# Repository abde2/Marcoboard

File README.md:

# Marcoboard
 This is going to be my first deep delve into keyboard design. I am going to be creating most of this myself using ai03 PCB design guides and other guides that will help me along the way. This would be much simpler if I could use a pro micro and socket it onto the board but I need a total of 27 usable pins, along with it being a DIP package as I suck at soldering surface mount chips.
 The keyboard itself will be a 65% keyboard that will utilise 2 rotary encoders, with push switches, along with an OLED screen inbetween them so that you can easily tell which layer you are on. 
 RGB lighting may also be included if I can figure it out but it isn't exactly necessary. I may only create a capslock light for it.
 This is going to be useful for flashing the bootloader onto it. https://www.instructables.com/id/Burning-Arduino-Bootloader-to-Atmega-32A-PU-Using-/
 http://vusb.wikidot.com/hardware
 https://www.reddit.com/r/MechanicalKeyboards/comments/5xubd7/adding_oled_display_to_your_build_using_qmk/

 Current Progress:
 The first revision of the development board is finished. This is so that I can hand solder the components because I won't be able to manage QFN packages.

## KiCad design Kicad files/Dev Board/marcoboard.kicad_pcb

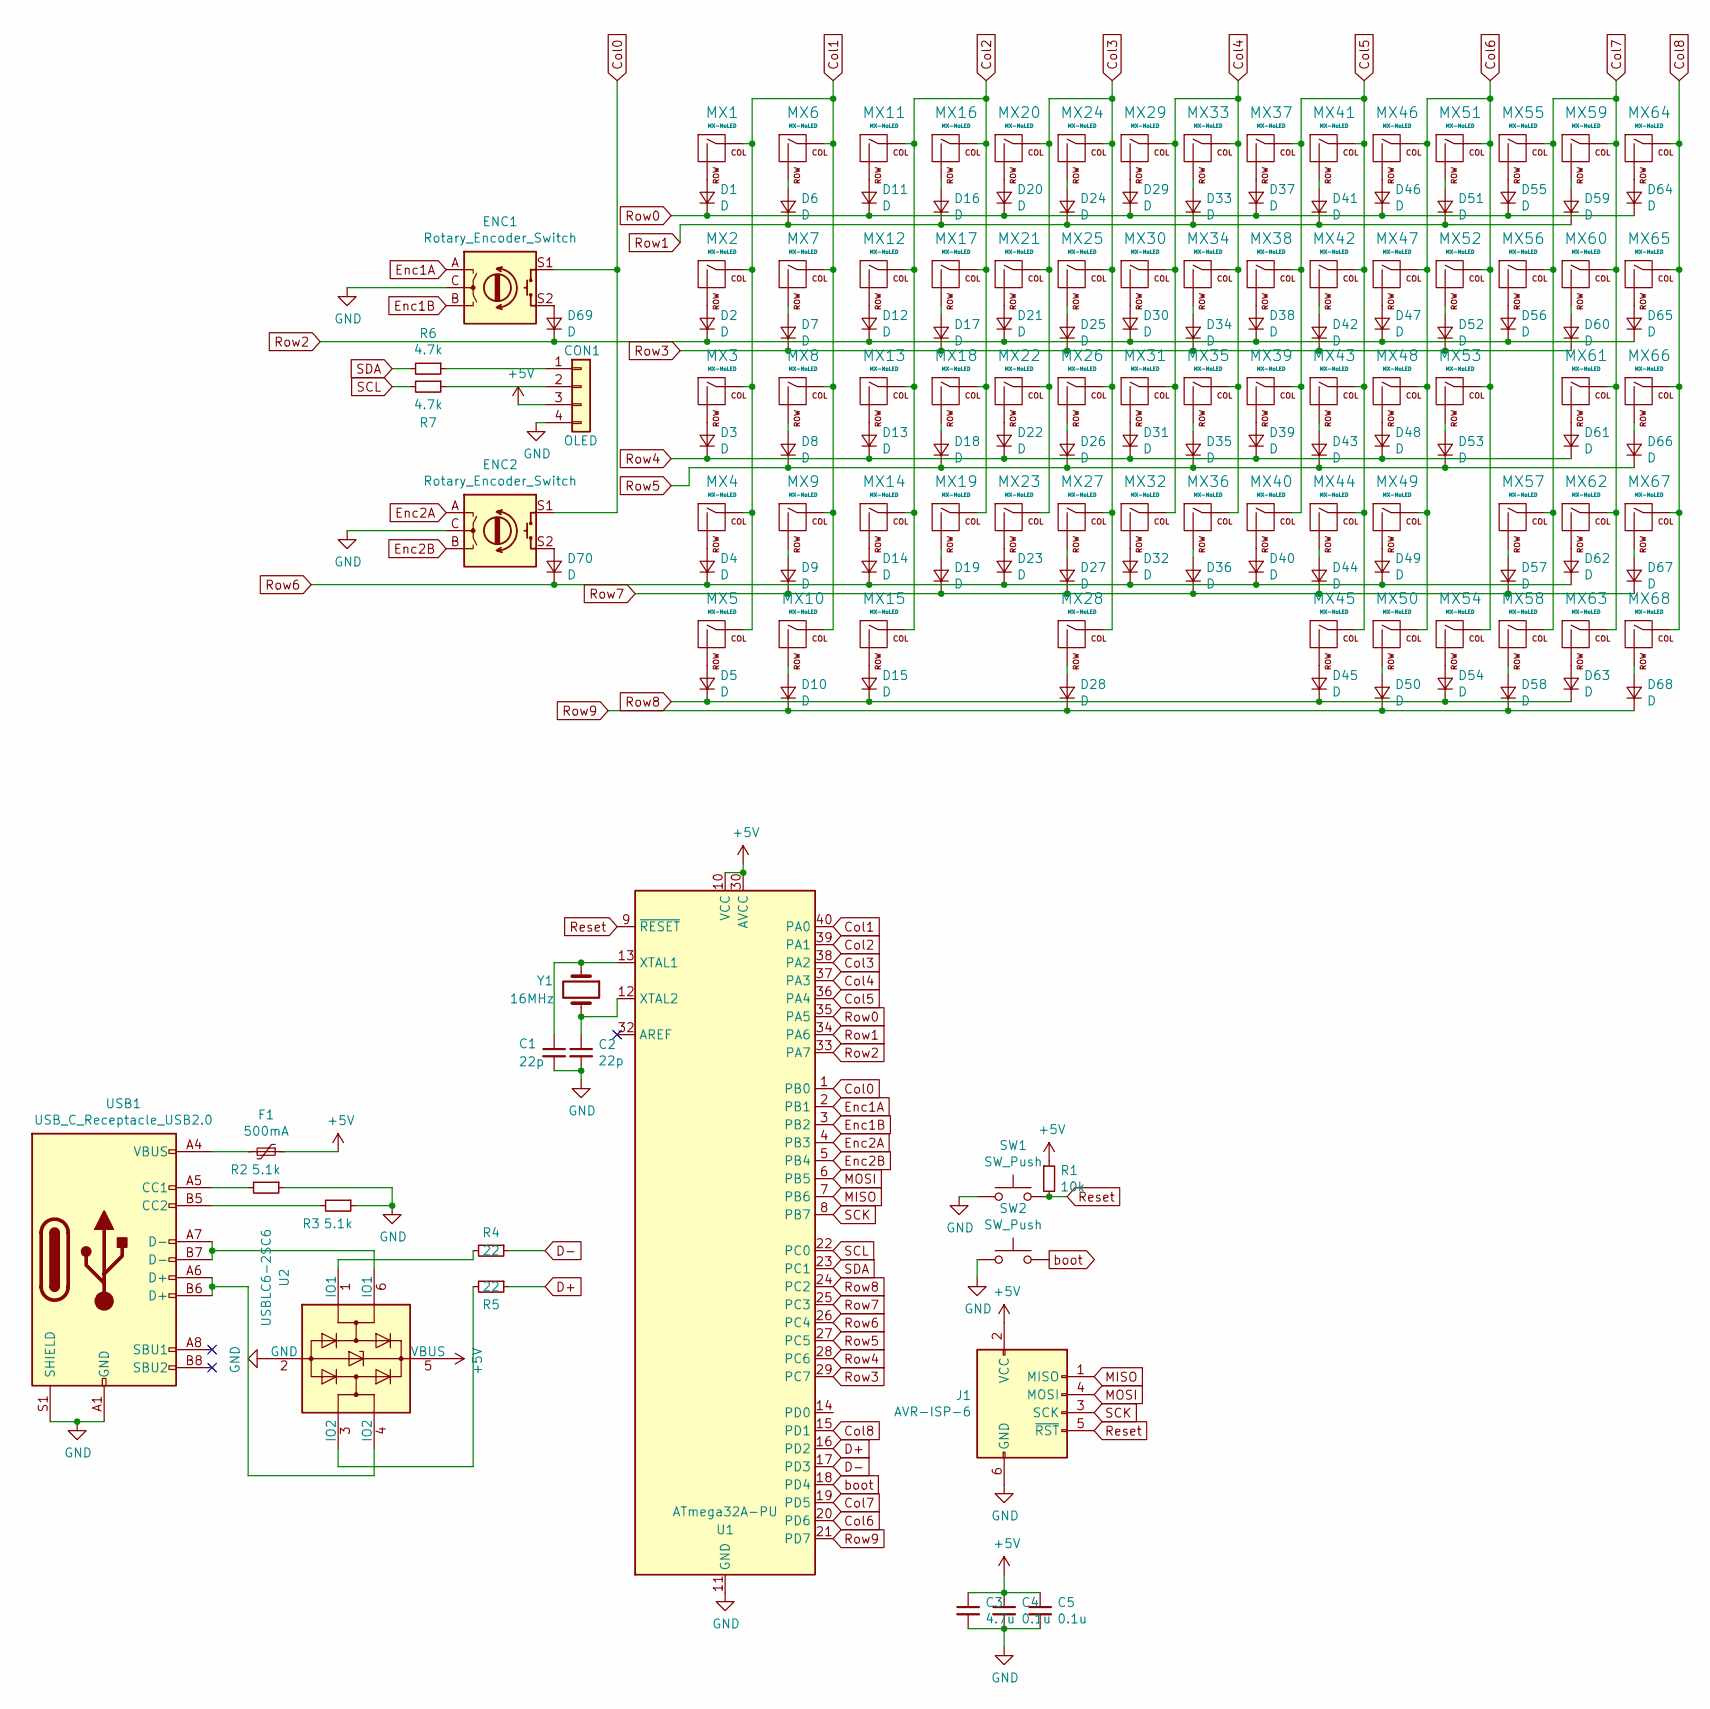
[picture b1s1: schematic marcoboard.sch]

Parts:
C1, C2: 22p; C_0603_1608Metric
C3: 4.7u; C_0603_1608Metric
C4, C5: 0.1u; C_0603_1608Metric
CON1: OLED; 128x32OLED
D1, D2, D3, D4, D5, D6, D7, D8, D9, D10, D11, D12, D13, D14, D15, D16, D17, D18, D19, D20, D21, D22, D23, D24, D25, D26, D27, D28, D29, D30, D31, D32, D33, D34, D35, D36, D37, D38, D39, D40, D41, D42, D43, D44, D45, D46, D47, D48, D49, D50, D51, D52, D53, D54, D55, D56, D57, D58, D59, D60, D61, D62, D63, D64, D65, D66, D67, D68, D69, D70: D; D_SC79
ENC1, ENC2: Rotary_Encoder_Switch; RotaryEncoder_Alps_EC11E-Switch_Vertical_H20mm
F1: 500mA; Fuse_0603_1608Metric
J1: AVR-ISP-6; PinHeader_2x03_P2.00mm_Vertical
MX1, MX6, MX7, MX8, MX9, MX11, MX12, MX13, MX14, MX16, MX17, MX18, MX19, MX20, MX21, MX22, MX23, MX24, MX25, MX26, MX27, MX29, MX30, MX31, MX32, MX33, MX34, MX35, MX36, MX37, MX38, MX39, MX40, MX41, MX42, MX43, MX44, MX45, MX46, MX47, MX48, MX49, MX50, MX51, MX52, MX53, MX54, MX55, MX56, MX58, MX62, MX63, MX64, MX65, MX66, MX67, MX68: MX-NoLED; SW_Cherry_MX_1.00u_Plate
MX2, MX60: MX-NoLED; SW_Cherry_MX_1.50u_Plate
MX3, MX57: MX-NoLED; SW_Cherry_MX_1.75u_Plate
MX4, MX61: MX-NoLED; SW_Cherry_MX_2.25u_Plate
MX5, MX10, MX15: MX-NoLED; SW_Cherry_MX_1.25u_Plate
MX28: MX-NoLED; SW_Cherry_MX_6.25u_Plate
MX59: MX-NoLED; SW_Cherry_MX_2.00u_Plate
R1: 10k; R_0603_1608Metric
R2, R3: 5.1k; R_0603_1608Metric
R4, R5: 22; R_0603_1608Metric
R6, R7: 4.7k; R_0603_1608Metric
SW1, SW2: SW_Push; SW_PUSH_6mm
U1: ATmega32A-PU; DIP-40_W15.24mm
U2: USBLC6-2SC6; SOT-23-6
USB1: USB_C_Receptacle_USB2.0; USB_C_GCT_USB4085
Y1: 16MHz; Crystal_HC49-U_Vertical

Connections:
+5V: C3.1, C4.1, C5.1, CON1.3, F1.1, J1.2 (VCC), R1.1, U1.10 (VCC), U1.30 (AVCC), U2.5 (VBUS)
Col0: ENC1.S1, ENC2.S1, U1.1 (PB0)
Col1: MX1.1 (COL), MX2.1 (COL), MX3.1 (COL), MX4.1 (COL), MX5.1 (COL), MX6.1 (COL), MX7.1 (COL), MX8.1 (COL), MX9.1 (COL), MX10.1 (COL), U1.40 (PA0)
Col2: MX11.1 (COL), MX12.1 (COL), MX13.1 (COL), MX14.1 (COL), MX15.1 (COL), MX16.1 (COL), MX17.1 (COL), MX18.1 (COL), MX19.1 (COL), U1.39 (PA1)
Col3: MX20.1 (COL), MX21.1 (COL), MX22.1 (COL), MX23.1 (COL), MX24.1 (COL), MX25.1 (COL), MX26.1 (COL), MX27.1 (COL), MX28.1 (COL), U1.38 (PA2)
Col4: MX29.1 (COL), MX30.1 (COL), MX31.1 (COL), MX32.1 (COL), MX33.1 (COL), MX34.1 (COL), MX35.1 (COL), MX36.1 (COL), U1.37 (PA3)
Col5: MX37.1 (COL), MX38.1 (COL), MX39.1 (COL), MX40.1 (COL), MX41.1 (COL), MX42.1 (COL), MX43.1 (COL), MX44.1 (COL), MX45.1 (COL), U1.36 (PA4)
Col6: MX46.1 (COL), MX47.1 (COL), MX48.1 (COL), MX49.1 (COL), MX50.1 (COL), MX51.1 (COL), MX52.1 (COL), MX53.1 (COL), MX54.1 (COL), U1.20 (PD6)
Col7: MX55.1 (COL), MX56.1 (COL), MX57.1 (COL), MX58.1 (COL), MX59.1 (COL), MX60.1 (COL), MX61.1 (COL), MX62.1 (COL), MX63.1 (COL), U1.19 (PD5)
Col8: MX64.1 (COL), MX65.1 (COL), MX66.1 (COL), MX67.1 (COL), MX68.1 (COL), U1.15 (PD1)
D+: R5.1, U1.16 (PD2)
D-: R4.1, U1.17 (PD3)
Enc1A: ENC1.A, U1.2 (PB1)
Enc1B: ENC1.B, U1.3 (PB2)
Enc2A: ENC2.A, U1.4 (PB3)
Enc2B: ENC2.B, U1.5 (PB4)
GND: C1.2, C2.2, C3.2, C4.2, C5.2, CON1.4, ENC1.C, ENC2.C, J1.6 (GND), R2.1, R3.1, SW1.1, SW2.1, U1.11 (GND), U1.31 (GND), U2.2 (GND), USB1.A1 (GND), USB1.A12 (GND), USB1.B1 (GND), USB1.B12 (GND), USB1.S1 (SHIELD)
MISO: J1.1 (MISO), U1.7 (PB6)
MOSI: J1.4 (MOSI), U1.6 (PB5)
unnamed: C1.1, U1.13 (XTAL1), Y1.1
unnamed: C2.1, U1.12 (XTAL2), Y1.2
unnamed: CON1.1, R6.1
unnamed: CON1.2, R7.1
unnamed: D1.2 (A), MX1.2 (ROW)
unnamed: D2.2 (A), MX2.2 (ROW)
unnamed: D3.2 (A), MX3.2 (ROW)
unnamed: D4.2 (A), MX4.2 (ROW)
unnamed: D5.2 (A), MX5.2 (ROW)
unnamed: D6.2 (A), MX6.2 (ROW)
unnamed: D7.2 (A), MX7.2 (ROW)
unnamed: D8.2 (A), MX8.2 (ROW)
unnamed: D9.2 (A), MX9.2 (ROW)
unnamed: D10.2 (A), MX10.2 (ROW)
unnamed: D11.2 (A), MX11.2 (ROW)
unnamed: D12.2 (A), MX12.2 (ROW)
unnamed: D13.2 (A), MX13.2 (ROW)
unnamed: D14.2 (A), MX14.2 (ROW)
unnamed: D15.2 (A), MX15.2 (ROW)
unnamed: D16.2 (A), MX16.2 (ROW)
unnamed: D17.2 (A), MX17.2 (ROW)
unnamed: D18.2 (A), MX18.2 (ROW)
unnamed: D19.2 (A), MX19.2 (ROW)
unnamed: D20.2 (A), MX20.2 (ROW)
unnamed: D21.2 (A), MX21.2 (ROW)
unnamed: D22.2 (A), MX22.2 (ROW)
unnamed: D23.2 (A), MX23.2 (ROW)
unnamed: D24.2 (A), MX24.2 (ROW)
unnamed: D25.2 (A), MX25.2 (ROW)
unnamed: D26.2 (A), MX26.2 (ROW)
unnamed: D27.2 (A), MX27.2 (ROW)
unnamed: D28.2 (A), MX28.2 (ROW)
unnamed: D29.2 (A), MX29.2 (ROW)
unnamed: D30.2 (A), MX30.2 (ROW)
unnamed: D31.2 (A), MX31.2 (ROW)
unnamed: D32.2 (A), MX32.2 (ROW)
unnamed: D33.2 (A), MX33.2 (ROW)
unnamed: D34.2 (A), MX34.2 (ROW)
unnamed: D35.2 (A), MX35.2 (ROW)
unnamed: D36.2 (A), MX36.2 (ROW)
unnamed: D37.2 (A), MX37.2 (ROW)
unnamed: D38.2 (A), MX38.2 (ROW)
unnamed: D39.2 (A), MX39.2 (ROW)
unnamed: D40.2 (A), MX40.2 (ROW)
unnamed: D41.2 (A), MX41.2 (ROW)
unnamed: D42.2 (A), MX42.2 (ROW)
unnamed: D43.2 (A), MX43.2 (ROW)
unnamed: D44.2 (A), MX44.2 (ROW)
unnamed: D45.2 (A), MX45.2 (ROW)
unnamed: D46.2 (A), MX46.2 (ROW)
unnamed: D47.2 (A), MX47.2 (ROW)
unnamed: D48.2 (A), MX48.2 (ROW)
unnamed: D49.2 (A), MX49.2 (ROW)
unnamed: D50.2 (A), MX50.2 (ROW)
unnamed: D51.2 (A), MX51.2 (ROW)
unnamed: D52.2 (A), MX52.2 (ROW)
unnamed: D53.2 (A), MX53.2 (ROW)
unnamed: D54.2 (A), MX54.2 (ROW)
unnamed: D55.2 (A), MX55.2 (ROW)
unnamed: D56.2 (A), MX56.2 (ROW)
unnamed: D57.2 (A), MX57.2 (ROW)
unnamed: D58.2 (A), MX58.2 (ROW)
unnamed: D59.2 (A), MX59.2 (ROW)
unnamed: D60.2 (A), MX60.2 (ROW)
unnamed: D61.2 (A), MX61.2 (ROW)
unnamed: D62.2 (A), MX62.2 (ROW)
unnamed: D63.2 (A), MX63.2 (ROW)
unnamed: D64.2 (A), MX64.2 (ROW)
unnamed: D65.2 (A), MX65.2 (ROW)
unnamed: D66.2 (A), MX66.2 (ROW)
unnamed: D67.2 (A), MX67.2 (ROW)
unnamed: D68.2 (A), MX68.2 (ROW)
unnamed: D69.2 (A), ENC1.S2
unnamed: D70.2 (A), ENC2.S2
unnamed: F1.2, USB1.A4 (VBUS), USB1.A9 (VBUS), USB1.B4 (VBUS), USB1.B9 (VBUS)
unnamed: R2.2, USB1.A5 (CC1)
unnamed: R3.2, USB1.B5 (CC2)
unnamed: R4.2, U2.1 (IO1)
unnamed: R5.2, U2.3 (IO2)
unnamed: U2.4 (IO2), USB1.A6 (D+), USB1.B6 (D+)
unnamed: U2.6 (IO1), USB1.A7 (D-), USB1.B7 (D-)
Reset: J1.5 (~RST), R1.2, SW1.2, U1.9 (~RESET)
Row0: D1.1 (K), D11.1 (K), D20.1 (K), D29.1 (K), D37.1 (K), D46.1 (K), D55.1 (K), D64.1 (K), U1.35 (PA5)
Row1: D6.1 (K), D16.1 (K), D24.1 (K), D33.1 (K), D41.1 (K), D51.1 (K), D59.1 (K), U1.34 (PA6)
Row2: D2.1 (K), D12.1 (K), D21.1 (K), D30.1 (K), D38.1 (K), D47.1 (K), D56.1 (K), D65.1 (K), D69.1 (K), U1.33 (PA7)
Row3: D7.1 (K), D17.1 (K), D25.1 (K), D34.1 (K), D42.1 (K), D52.1 (K), D60.1 (K), U1.29 (PC7)
Row4: D3.1 (K), D13.1 (K), D22.1 (K), D31.1 (K), D39.1 (K), D48.1 (K), D61.1 (K), U1.28 (PC6)
Row5: D8.1 (K), D18.1 (K), D26.1 (K), D35.1 (K), D43.1 (K), D53.1 (K), D66.1 (K), U1.27 (PC5)
Row6: D4.1 (K), D14.1 (K), D23.1 (K), D32.1 (K), D40.1 (K), D49.1 (K), D62.1 (K), D70.1 (K), U1.26 (PC4)
Row7: D9.1 (K), D19.1 (K), D27.1 (K), D36.1 (K), D44.1 (K), D57.1 (K), D67.1 (K), U1.25 (PC3)
Row8: D5.1 (K), D15.1 (K), D45.1 (K), D54.1 (K), D63.1 (K), U1.24 (PC2)
Row9: D10.1 (K), D28.1 (K), D50.1 (K), D58.1 (K), D68.1 (K), U1.21 (PD7)
SCK: J1.3 (SCK), U1.8 (PB7)
SCL: R7.2, U1.22 (PC0)
SDA: R6.2, U1.23 (PC1)
boot: SW2.2, U1.18 (PD4)

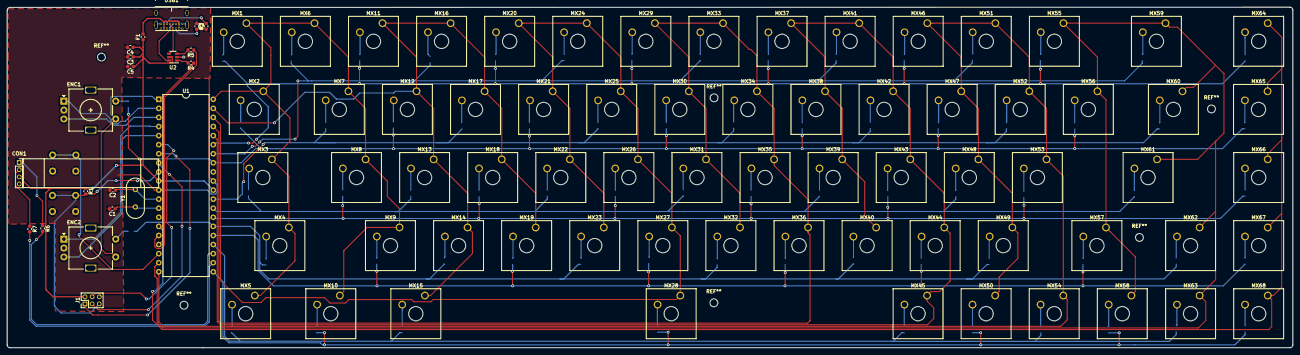
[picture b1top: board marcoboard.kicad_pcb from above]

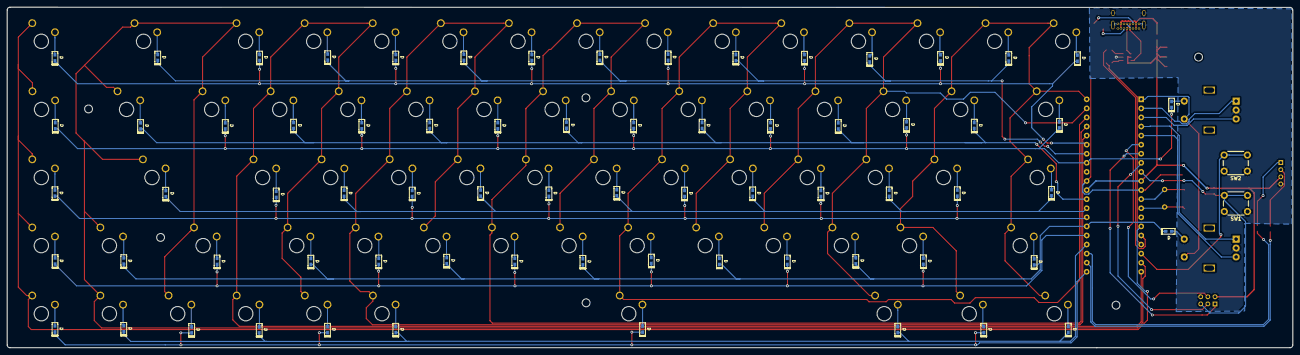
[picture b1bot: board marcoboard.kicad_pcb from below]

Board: 2 copper layers, 359.7 x 95.2 mm, 161 parts (72 on the bottom side), 115 nets.

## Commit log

2020-08-17 Create Kicad_files
2020-08-17 Add submodules
2020-08-17 libraries
2020-08-17 kicad
2020-08-18 Removed OLED
2020-08-18 Board updates
2020-08-19 Dev board difference added
2020-08-20 Routing
2020-08-21 PCB finished
2020-08-21 Finished dev pcb
2020-08-23 Case design
2020-08-24 case
2020-09-14 Case files
2020-09-16 huhu
2020-09-19 hoids
2020-09-21 more and more and more and more and more and more case stuff
2020-09-21 plate
2020-09-24 more stuff
2020-09-24 more shtuff
